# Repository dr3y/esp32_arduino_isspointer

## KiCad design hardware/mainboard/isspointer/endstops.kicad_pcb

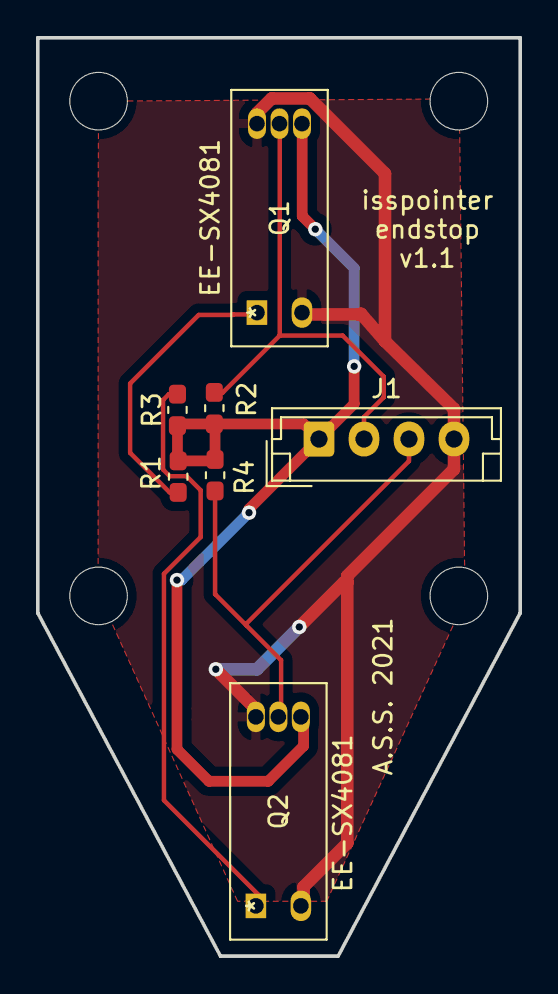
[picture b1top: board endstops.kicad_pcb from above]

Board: 2 copper layers, 26.8 x 51.0 mm, 7 parts (0 on the bottom side), 6 nets.

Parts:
J1: Conn_01x04_Female; JST_EH_B4B-EH-A_1x04_P2.50mm_Vertical
Q1, Q2: EE-SX4081
R1, R3: 330(5%); R_0603_1608Metric_Pad1.05x0.95mm_HandSolder
R2, R4: 4.7K(5%); R_0603_1608Metric_Pad1.05x0.95mm_HandSolder

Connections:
+5V: J1.1, Q1.3, Q2.3, R1.1, R2.1, R3.1, R4.1
/END_V1: J1.2, Q1.4, R2.2
/END_V2: J1.3, Q2.4, R4.2
GND: J1.4, Q1.2, Q1.5, Q2.2, Q2.5
unnamed: Q1.1, R1.2
unnamed: Q2.1, R3.2

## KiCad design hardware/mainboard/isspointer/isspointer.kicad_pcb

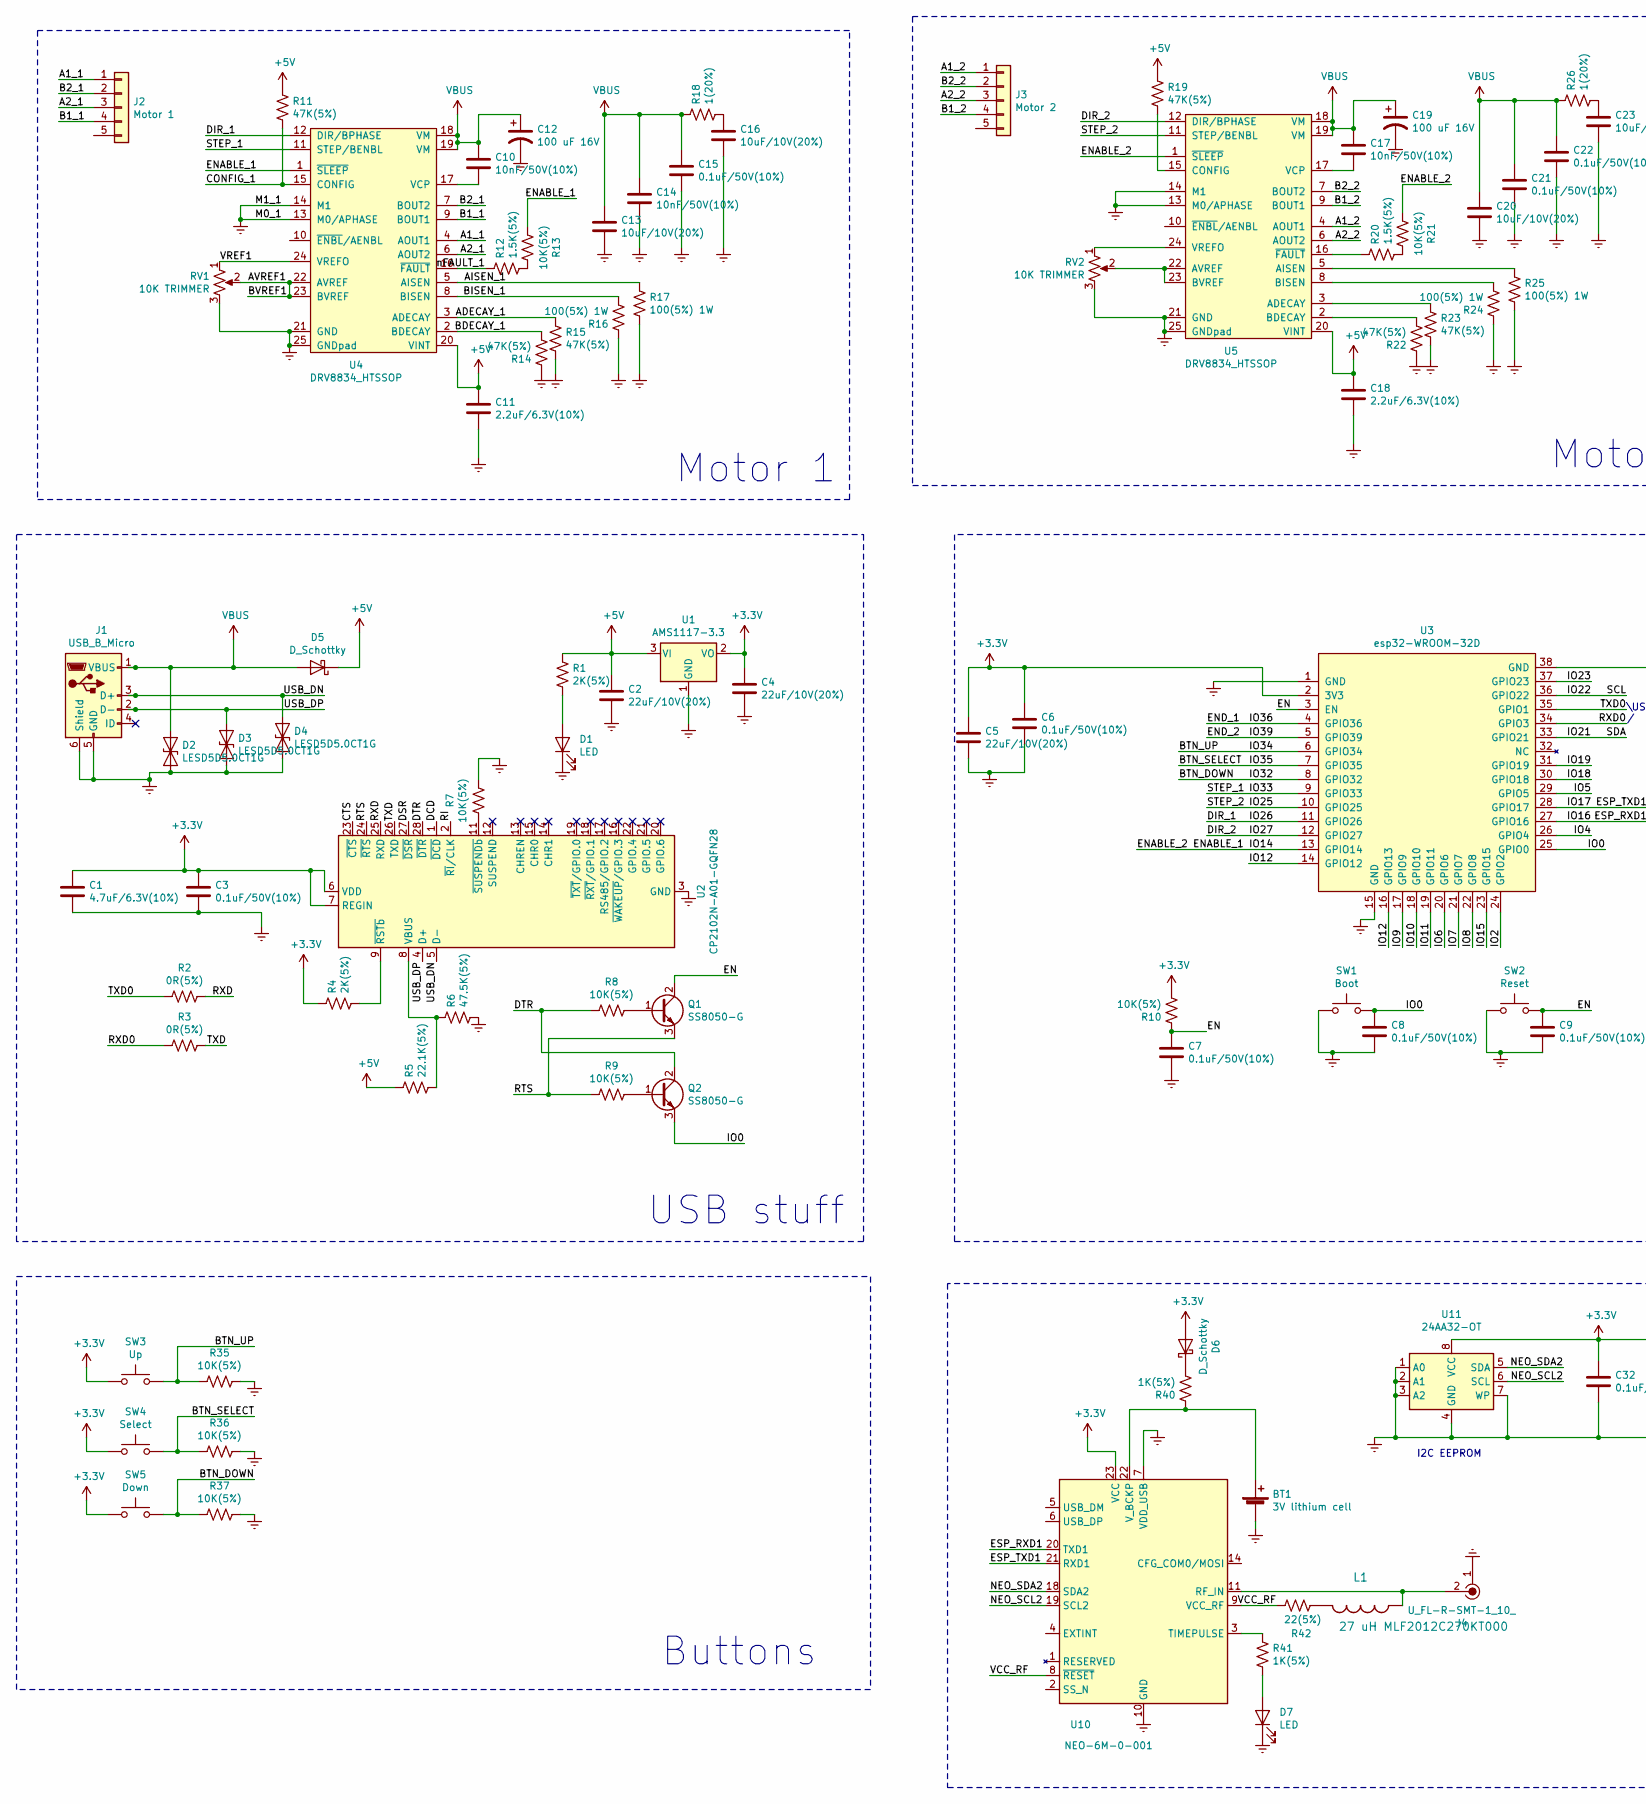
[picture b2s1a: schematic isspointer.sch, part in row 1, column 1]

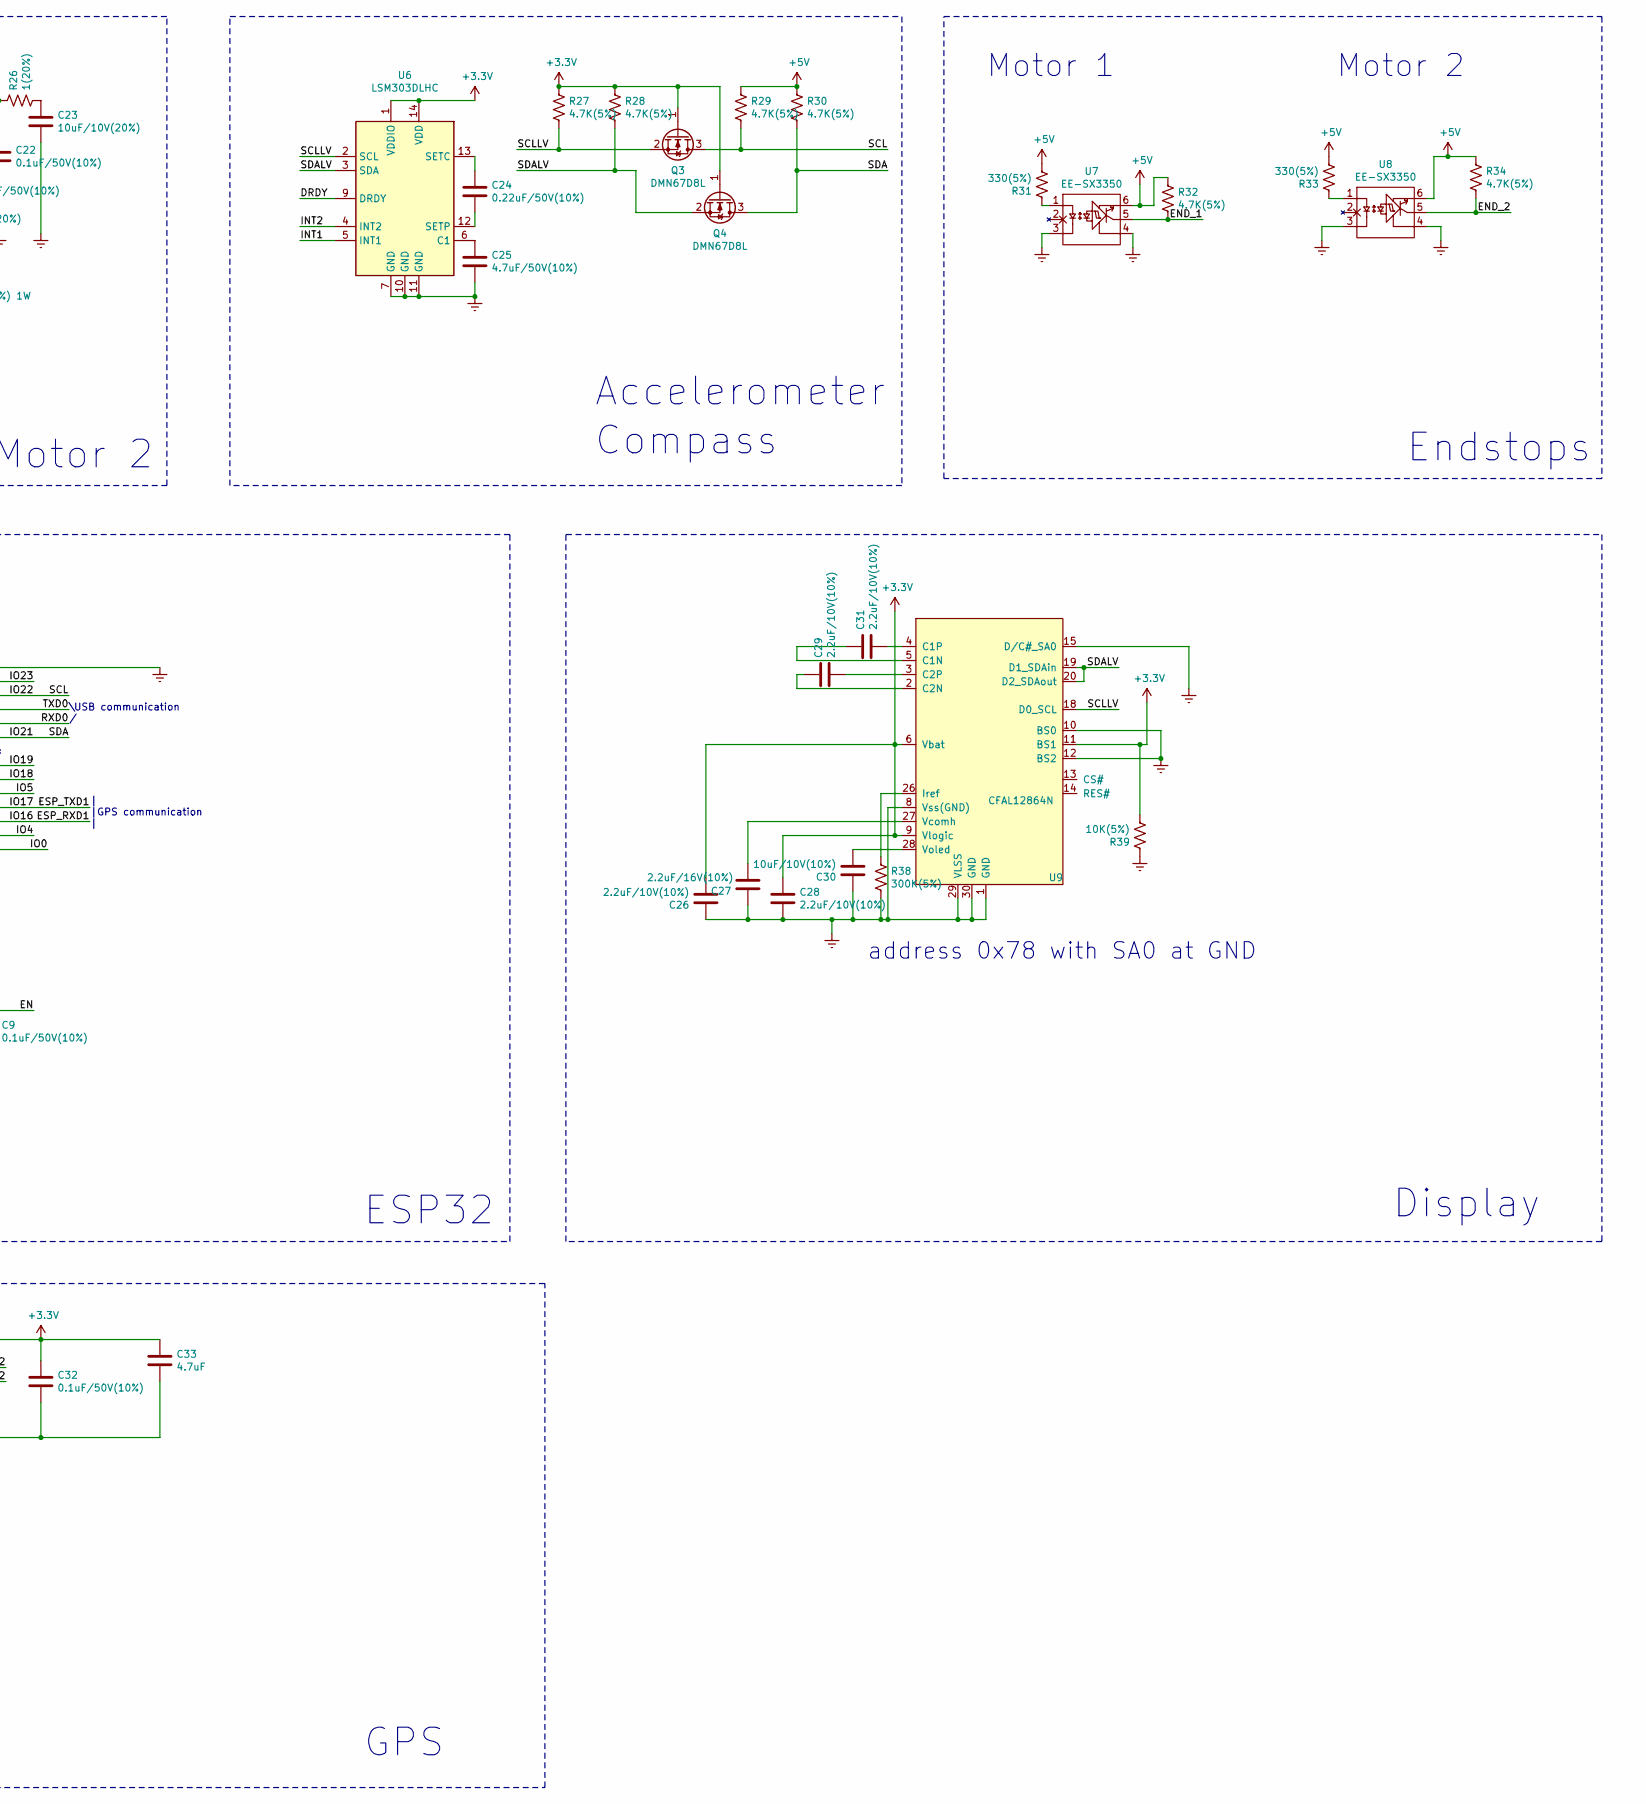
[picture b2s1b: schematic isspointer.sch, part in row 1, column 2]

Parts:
BT1: 3V lithium cell; MS412FE_FL26E
C1: 4.7uF/6.3V(10%); C_0603_1608Metric_Pad1.05x0.95mm_HandSolder
C2, C4, C5: 22uF/10V(20%); C_1206_3216Metric_Pad1.42x1.75mm_HandSolder
C3, C6, C7, C8, C9, C15, C21, C22, C32: 0.1uF/50V(10%); C_0603_1608Metric_Pad1.05x0.95mm_HandSolder
C10, C14, C17: 10nF/50V(10%); C_0402_1005Metric
C11, C18: 2.2uF/6.3V(10%); C_0402_1005Metric
C12, C19: 100 uF 16V; CP_Elec_6.3x4.9
C13, C16, C23: 10uF/10V(20%); C_0603_1608Metric_Pad1.05x0.95mm_HandSolder
C20: 10uF/10V(20%); C_0402_1005Metric
C24: 0.22uF/50V(10%); C_0603_1608Metric_Pad1.05x0.95mm_HandSolder
C25: 4.7uF/50V(10%); C_0603_1608Metric_Pad1.05x0.95mm_HandSolder
C26, C28, C29, C31: 2.2uF/10V(10%); C_0603_1608Metric_Pad1.05x0.95mm_HandSolder
C27: 2.2uF/16V(10%); C_0603_1608Metric_Pad1.05x0.95mm_HandSolder
C30: 10uF/10V(10%); C_0603_1608Metric_Pad1.05x0.95mm_HandSolder
C33: 4.7uF; C_0603_1608Metric_Pad1.05x0.95mm_HandSolder
D1, D7: LED; D_0603_1608Metric
D2, D3, D4: LESD5D5.0CT1G; D_SOD-523
D5, D6: D_Schottky; D_SOD-323_HandSoldering
J1: USB_B_Micro; USB_Micro-B_Molex_47346-0001
J2: Motor 1; JST_XH_B5B-XH-A_1x05_P2.50mm_Vertical
J3: Motor 2; JST_XH_B5B-XH-A_1x05_P2.50mm_Vertical
J4: U_FL-R-SMT-1_10_; Coax_Conn_U.FL; MPN U.FL-R-SMT-1(10); Digi-Key_PN H11891CT-ND
L1: 27 uH MLF2012C270KT000; L_0805_2012Metric_Pad1.15x1.40mm_HandSolder
Q1, Q2: SS8050-G; SOT-23
Q3, Q4: DMN67D8L; SOT-23
R1, R4: 2K(5%); R_0603_1608Metric_Pad1.05x0.95mm_HandSolder
R2, R3: 0R(5%); R_0603_1608Metric_Pad1.05x0.95mm_HandSolder
R5: 22.1K(5%); R_0603_1608Metric_Pad1.05x0.95mm_HandSolder
R6: 47.5K(5%); R_0603_1608Metric_Pad1.05x0.95mm_HandSolder
R7, R8, R9, R10, R13, R21, R35, R36, R37, R39: 10K(5%); R_0603_1608Metric_Pad1.05x0.95mm_HandSolder
R11, R14, R15, R19, R22, R23: 47K(5%); R_0603_1608Metric_Pad1.05x0.95mm_HandSolder
R12, R20: 1.5K(5%); R_0603_1608Metric_Pad1.05x0.95mm_HandSolder
R16, R17, R24, R25: 100(5%) 1W; R_2512_6332Metric_Pad1.52x3.35mm_HandSolder
R18, R26: 1(20%); R_0603_1608Metric_Pad1.05x0.95mm_HandSolder
R27, R28, R29, R30, R32, R34: 4.7K(5%); R_0603_1608Metric_Pad1.05x0.95mm_HandSolder
R31, R33: 330(5%); R_0603_1608Metric_Pad1.05x0.95mm_HandSolder
R38: 300K(5%); R_0603_1608Metric_Pad1.05x0.95mm_HandSolder
R40, R41: 1K(5%); R_0603_1608Metric_Pad1.05x0.95mm_HandSolder
R42: 22(5%); R_0603_1608Metric_Pad1.05x0.95mm_HandSolder
RV1, RV2: 10K TRIMMER; Trimpot_3.8mmx3.6mm_TC33X-2-103E
SW1: Boot; SW_SPST_CK_RS282G05A3
SW2: Reset; SW_SPST_CK_RS282G05A3
SW3: Up; SW_SPST_B3S-1000
SW4: Select; SW_SPST_B3S-1000
SW5: Down; SW_SPST_B3S-1000
U1: AMS1117-3.3; SOT-223-3_TabPin2
U2: CP2102N-A01-GQFN28; QFN-28-1EP_5x5mm_P0.5mm_EP3.35x3.35mm
U3: esp32-WROOM-32D; ESP32-WROOM-32D
U4, U5: DRV8834_HTSSOP; DRV8834PWPR
U6: LSM303DLHC; LGA-14_3x5mm_P0.8mm_LayoutBorder1x6y
U7, U8: EE-SX3350
U9: CFAL12864N; CFAL12864N_oled
U10: NEO-6M-0-001; ublox_NEO
U11: 24AA32-OT; SOIC-8_3.9x4.9mm_P1.27mm

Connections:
+3V3: C1.1, C3.1, C4.1, C5.1, C6.1, C26.2, C28.1, C32.1, C33.1, D6.2 (A), Q3.1 (G), Q4.1 (G), R4.2, R10.1, R27.1, R28.1, R39.2, SW3.1, SW4.1, SW5.1, U1.2 (VO), U2.6 (VDD), U2.7 (REGIN), U3.2 (3V3), U6.1 (VDDIO), U6.14 (VDD), U9.6 (Vbat), U9.9 (Vlogic), U9.11 (BS1), U10.23 (VCC), U11.8 (VCC)
+5V: C2.1, C11.1, C18.1, D5.1 (K), R1.1, R5.2, R11.1, R19.1, R29.1, R30.1, R31.2, R32.1, R33.2, R34.1, U1.3 (VI), U4.20 (VINT), U5.20 (VINT), U7.6, U8.6
/A1_1: J2.1, U4.4 (AOUT1)
/A1_2: J3.1, U5.4 (AOUT1)
/A2_1: J2.3, U4.6 (AOUT2)
/A2_2: J3.3, U5.6 (AOUT2)
/ADECAY_1: R15.1, U4.3 (ADECAY)
/AISEN_1: R17.1, U4.5 (AISEN)
/AVREF1: RV1.2, U4.22 (AVREF), U4.23 (BVREF)
/B1_1: J2.4, U4.9 (BOUT1)
/B1_2: J3.4, U5.9 (BOUT1)
/B2_1: J2.2, U4.7 (BOUT2)
/B2_2: J3.2, U5.7 (BOUT2)
/BDECAY_1: R14.2, U4.2 (BDECAY)
/BISEN_1: R16.2, U4.8 (BISEN)
/BTN_DOWN: R37.2, SW5.2, U3.8 (GPIO32)
/BTN_SELECT: R36.2, SW4.2, U3.7 (GPIO35)
/BTN_UP: R35.2, SW3.2, U3.6 (GPIO34)
/CONFIG_1: R11.2, U4.15 (CONFIG)
/CTS: U2.23 (~CTS)
/DCD: U2.1 (~DCD)
/DIR_1: U3.11 (GPIO26), U4.12 (DIR/BPHASE)
/DIR_2: U3.12 (GPIO27), U5.12 (DIR/BPHASE)
/DRDY: U6.9 (DRDY)
/DSR: U2.27 (~DSR)
/DTR: Q2.2 (C), R8.2, U2.28 (~DTR)
/EN: C7.1, C9.1, Q1.2 (C), R10.2, SW2.2, U3.3 (EN)
/ENABLE_1: R13.2, R21.2, U3.13 (GPIO14), U4.1 (~SLEEP), U5.1 (~SLEEP)
/END_1: R32.2, U3.4 (GPIO36), U7.5
/END_2: R34.2, U3.5 (GPIO39), U8.5
/ESP_RXD1: U3.27 (GPIO16), U10.20 (TXD1)
/ESP_TXD1: U3.28 (GPIO17), U10.21 (RXD1)
/INT1: U6.5 (INT1)
/INT2: U6.4 (INT2)
/IO0: C8.1, Q2.3 (E), SW1.2, U3.25 (GPIO0)
/IO2: U3.24 (GPIO2)
/IO4: U3.26 (GPIO4)
/IO5: U3.29 (GPIO5)
/IO6: U3.20 (GPIO6)
/IO7: U3.21 (GPIO7)
/IO8: U3.22 (GPIO8)
/IO9: U3.17 (GPIO9)
/IO10: U3.18 (GPIO10)
/IO11: U3.19 (GPIO11)
/IO12: U3.14 (GPIO12), U3.16 (GPIO13)
/IO15: U3.23 (GPIO15)
/IO18: U3.30 (GPIO18)
/IO19: U3.31 (GPIO19)
/IO21: Q4.3 (D), R30.2, U3.33 (GPIO21)
/IO22: Q3.3 (D), R29.2, U3.36 (GPIO22)
/IO23: U3.37 (GPIO23)
/IO25: U3.10 (GPIO25), U5.11 (STEP/BENBL)
/IO33: U3.9 (GPIO33), U4.11 (STEP/BENBL)
/NEO_SCL2: U10.19 (SCL2), U11.6 (SCL)
/NEO_SDA2: U10.18 (SDA2), U11.5 (SDA)
/RI: U2.2 (~RI~/CLK)
/RTS: Q1.3 (E), R9.2, U2.24 (~RTS)
/RXD: R2.1, U2.25 (RXD)
/RXD0: R3.2, U3.34 (GPIO3)
/SCLLV: Q3.2 (S), R27.2, U6.2 (SCL), U9.18 (D0_SCL)
/SDALV: Q4.2 (S), R28.2, U6.3 (SDA), U9.19 (D1_SDAin), U9.20 (D2_SDAout)
/TXD: R3.1, U2.26 (TXD)
/TXD0: R2.2, U3.35 (GPIO1)
/USB_DN: D4.1 (A1), J1.3 (D+), U2.5 (D-)
/USB_DP: D3.1 (A1), J1.2 (D-), U2.4 (D+)
/VCC_RF: R42.1, U10.8 (~RESET), U10.9 (VCC_RF)
/VREF1: RV1.1, U4.24 (VREFO)
/nFAULT_1: R12.1, U4.16 (~FAULT)
GNDREF: BT1.2 (-), C1.2, C2.2, C3.2, C4.2, C5.2, C6.2, C7.2, C8.2, C9.2, C11.2, C12.2, C13.2, C14.2, C15.2, C16.2, C18.2, C19.2, C20.2, C21.2, C22.2, C23.2, C25.2, C26.1, C27.1, C28.2, C30.1, C32.2, C33.2, D1.1 (K), D2.2 (A2), D3.2 (A2), D4.2 (A2), D7.1 (K), J1.5 (GND), J1.6 (Shield), J4.1, R6.1, R7.2, R14.1, R15.2, R16.1, R17.2, R22.1, R23.2, R24.1, R25.2, R35.1, R36.1, R37.1, R38.2, R39.1, RV1.3, RV2.3, SW1.1, SW2.1, U1.1 (GND), U2.3 (GND), U2.29 (GND), U3.1 (GND), U3.15 (GND), U3.38 (GND), U4.13 (M0/APHASE), U4.14 (M1), U4.21 (GND), U4.25 (GNDpad), U5.13 (M0/APHASE), U5.14 (M1), U5.21 (GND), U5.25 (GNDpad), U6.7 (GND), U6.10 (GND), U6.11 (GND), U7.3, U7.4, U8.3, U8.4, U9.1 (GND), U9.8 (Vss(GND)), U9.10 (BS0), U9.12 (BS2), U9.15 (D/C#_SA0), U9.29 (VLSS), U9.30 (GND), U10.7 (VDD_USB), U10.10 (GND), U10.12 (GND), U10.13 (GND), U10.24 (GND), U11.1 (A0), U11.2 (A1), U11.3 (A2), U11.4 (GND), U11.7 (WP)
unnamed: BT1.1 (+), R40.2, U10.22 (V_BCKP)
unnamed: C10.2, U4.17 (VCP)
unnamed: C16.1, R18.2
unnamed: C17.2, U5.17 (VCP)
unnamed: C23.1, R26.2
unnamed: C24.1, U6.13 (SETC)
unnamed: C24.2, U6.12 (SETP)
unnamed: C25.1, U6.6 (C1)
unnamed: C27.2, U9.27 (Vcomh)
unnamed: C29.1, U9.2 (C2N)
unnamed: C29.2, U9.3 (C2P)
unnamed: C30.2, U9.28 (Voled)
unnamed: C31.1, U9.5 (C1N)
unnamed: C31.2, U9.4 (C1P)
unnamed: D1.2 (A), R1.2
unnamed: D6.1 (K), R40.1
unnamed: D7.2 (A), R41.1
unnamed: J4.2, L1.1, U10.11 (RF_IN)
unnamed: L1.2, R42.2
unnamed: Q1.1 (B), R8.1
unnamed: Q2.1 (B), R9.1
unnamed: R4.1, U2.9 (~RSTb)
unnamed: R5.1, R6.2, U2.8 (VBUS)
unnamed: R7.1, U2.11 (~SUSPENDb)
unnamed: R12.2, R13.1
unnamed: R19.2, U5.15 (CONFIG)
unnamed: R20.1, U5.16 (~FAULT)
unnamed: R20.2, R21.1
unnamed: R22.2, U5.2 (BDECAY)
unnamed: R23.1, U5.3 (ADECAY)
unnamed: R24.2, U5.8 (BISEN)
unnamed: R25.1, U5.5 (AISEN)
unnamed: R31.1, U7.1
unnamed: R33.1, U8.1
unnamed: R38.1, U9.26 (Iref)
unnamed: R41.2, U10.3 (TIMEPULSE)
unnamed: RV2.1, U5.24 (VREFO)
unnamed: RV2.2, U5.22 (AVREF), U5.23 (BVREF)
VBUS: C10.1, C12.1, C13.1, C14.1, C15.1, C17.1, C19.1, C20.1, C21.1, C22.1, D2.1 (A1), D5.2 (A), J1.1 (VBUS), R18.1, R26.1, U4.18 (VM), U4.19 (VM), U5.18 (VM), U5.19 (VM)

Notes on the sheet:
Motor 1
Motor 2
USB stuff
ESP32
Accelerometer
Endstops
Compass
Display
address 0x78 with SA0 at GND
Buttons
GPS
| |GPS communication |
\USB communication /
I2C EEPROM

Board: 2 copper layers, 110 parts (103 on the bottom side), 88 nets, no tracks yet.

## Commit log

2020-01-20 intial commit; smartconfig
2020-01-20 test commit
2020-01-22 OLED display tests
2020-01-23 adding gps and eeprom
2020-01-24 stepper tests
2020-01-27 working steppers!
2020-01-28 aceel magnetometer
2020-01-29 fix libraries
2020-01-31 endstops!!
2020-02-03 menu stuff UNFINISHED
2020-02-09 working menu!!
2020-02-10 cleanup, lib_dep
2020-02-12 circuit board stuff
2020-02-12 esp32 pcb done
2020-02-13 minor
2020-02-13 stepper drivers
2020-02-21 endstops and accel circuit board
2020-02-21 display!
2020-02-24 3v battery
2020-02-24 some trace routing
2021-01-31 work MITAI bluetooth connection
2021-02-07 working wifi bluetooth provisioning
2021-02-15 GET request in progress
2021-06-16 working on perf board with endstops
2021-06-17 working homing and jogging

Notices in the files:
parts and their libraries:
Copyright 2021 Accelerated Designs. All rights reserved.
Copyright 2016 Accelerated Designs. All rights reserved.
